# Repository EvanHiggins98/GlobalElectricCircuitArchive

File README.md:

# GlobalElectricCircuitArchive
This is an archive of the Global Electric Circuit Project's code repositories. This Repository was made to allow for all involved code to be found in one place at the conclusion of the project.

Original repositories Global Electric Circuit project repositories can be found at:

| Repository                                                                  | Description         |
|:--------------------------------------------------------------------------- |:------------------  |
| [GlobalCircuit](https://github.com/chordtoll/GlobalCircuit)                    | PIC32 code          |
| [GECaux](https://github.com/chordtoll/GECaux)                                  | PIC16 code          |
| [GECutils](https://github.com/chordtoll/GECutils)                              | Python scripts      |
| [LocalElectricCircuit](https://github.com/CodyAnderson/LocalElectricCircuit)| Circuit board files |

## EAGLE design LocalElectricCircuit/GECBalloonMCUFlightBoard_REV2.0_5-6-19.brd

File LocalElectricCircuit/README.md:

# LocalElectricCircuit

This is the repository containing the Circuit board files for the Global Electric Circuit project.

Other Global Electric Circuit project repositories can be found at:

| Repository                                                                  | Description         |
|:--------------------------------------------------------------------------- |:------------------  |
| [GlobalCircuit](https://github.com/chordtoll/GlobalCircuit)                    | PIC32 code          |
| [GECaux](https://github.com/chordtoll/GECaux)                                  | PIC16 code          |
| [GECutils](https://github.com/chordtoll/GECutils)                              | Python scripts      |
| [LocalElectricCircuit](https://github.com/CodyAnderson/LocalElectricCircuit)| Circuit board files |

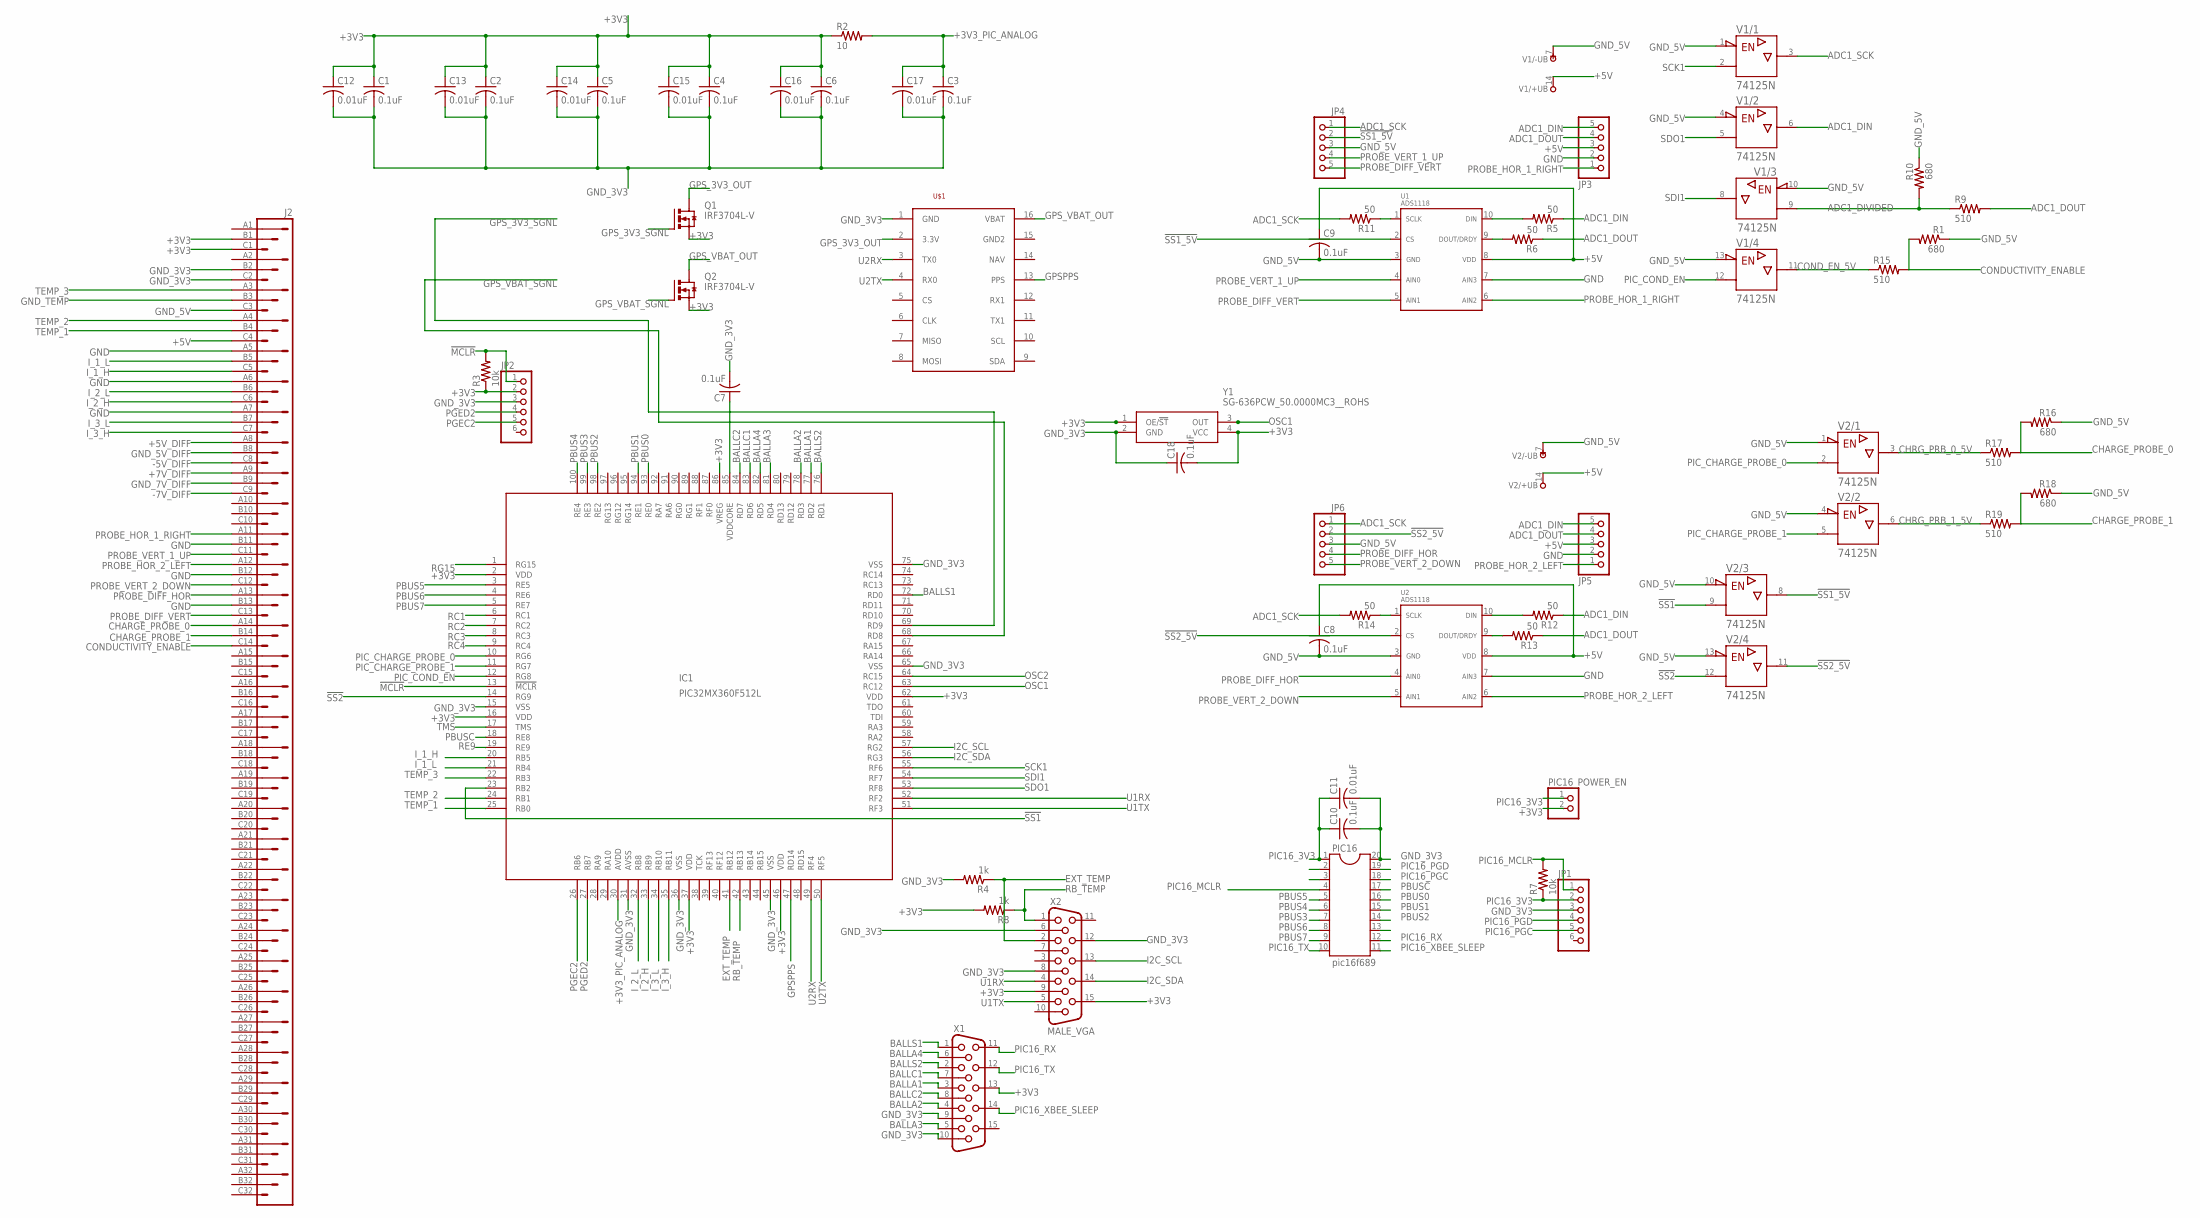
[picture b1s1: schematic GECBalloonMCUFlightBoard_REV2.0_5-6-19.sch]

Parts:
C1, C2, C3, C4, C5, C6, C7, C8, C9, C10, C18: 0.1uF; C1206
C11, C12, C13, C14, C15, C16, C17: 0.01uF; C1206
IC1: PIC32MX360F512L; TQFP100
J2: VG96KB
JP1, JP2: PINHD-1X6; 1X06
JP3, JP4, JP5, JP6: PINHD-1X5; 1X05
PIC16: pic16f689; DIL20
PIC16_POWER_EN: PINHD-1X2; 1X02
Q1, Q2: IRF3704L-V; TO262-V
R1, R10, R16, R18: 680; R1206
R2: 10; M1206
R3, R7: 10k; M1206
R4, R8: 1k; 0414/15
R5, R6, R11, R12, R13, R14: 50; M1206
R9, R15, R17, R19: 510; R1206
U1, U2: ADS1118; MSOP10
U$1: SPARKFUN_VENUS_GPS_BREAKOUT; SPARKFUN_BOARD
V1, V2: 74125N; DIL14
X1: HF15H; HDF15H
X2: MALE_VGA; MALE_PACKAGE
Y1: SG-636PCW_50.0000MC3__ROHS; SG-636

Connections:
!MCLR: IC1.13 (!MCLR), JP2.1, R3.2
!SS1: IC1.23 (RB2), V2.9 (A)
!SS1_5V: JP4.2, U1.2 (CS), V2.8 (Y)
!SS2: IC1.14 (RG9), V2.12 (A)
!SS2_5V: JP6.2, U2.2 (CS), V2.11 (Y)
+3V3: C1.1, C2.1, C4.1, C5.1, C6.1, C12.1, C13.1, C14.1, C15.1, C16.1, C18.2, IC1.2 (VDD), IC1.16 (VDD), IC1.37 (VDD), IC1.46 (VDD), IC1.62 (VDD), IC1.86 (VREG), J2.B1, J2.C1, JP2.2, PIC16_POWER_EN.2, Q1.3 (S), Q2.3 (S), R2.1, R3.1, R8.2, X1.13, X2.9, X2.15, Y1.1 (OE/!ST), Y1.4 (VCC)
+3V3_PIC_ANALOG: C3.1, C17.1, IC1.30 (AVDD), R2.2
+5V: C8.1, C9.1, J2.C4, JP3.3, JP5.3, U1.8 (VDD), U2.8 (VDD), V1.14 (+UB), V2.14 (+UB)
+5V_DIFF: J2.A8
+7V_DIFF: J2.A9
-5V_DIFF: J2.C8
-7V_DIFF: J2.C9
ADC1_DIN: JP3.5, JP5.5, R5.1, R12.1, V1.6 (Y)
ADC1_DIVIDED: R9.1, R10.2, V1.9 (A)
ADC1_DOUT: JP3.4, JP5.4, R6.1, R9.2, R13.1
ADC1_SCK: JP4.1, JP6.1, R11.2, R14.2, V1.3 (Y)
BALLA1: IC1.77 (RD2), X1.3
BALLA2: IC1.78 (RD3), X1.4
BALLA3: IC1.81 (RD4), X1.5
BALLA4: IC1.82 (RD5), X1.6
BALLC1: IC1.83 (RD6), X1.7
BALLC2: IC1.84 (RD7), X1.8
BALLS1: IC1.72 (RD0), X1.1
BALLS2: IC1.76 (RD1), X1.2
CHARGE_PROBE_0: J2.A14, R16.2, R17.2
CHARGE_PROBE_1: J2.B14, R18.2, R19.2
CHRG_PRB_0_5V: R17.1, V2.3 (Y)
CHRG_PRB_1_5V: R19.1, V2.6 (Y)
CONDUCTIVITY_ENABLE: J2.C14, R1.2, R15.2
COND_EN_5V: R15.1, V1.11 (Y)
EXT_TEMP: IC1.41 (RB12), R4.1, X2.2
GND: J2.A5, J2.A6, J2.A7, J2.B11, J2.B12, J2.B13, JP3.2, JP5.2, U1.7 (AIN3), U2.7 (AIN3)
GND_3V3: C1.2, C2.2, C3.2, C4.2, C5.2, C6.2, C7.2, C10.2, C11.2, C12.2, C13.2, C14.2, C15.2, C16.2, C17.2, C18.1, IC1.15 (VSS), IC1.31 (AVSS), IC1.36 (VSS), IC1.45 (VSS), IC1.65 (VSS), IC1.75 (VSS), J2.B2, J2.C2, JP1.3, JP2.3, PIC16.20, R4.2, U$1.1 (GND), X1.9, X1.10, X2.6, X2.8, X2.12, Y1.2 (GND)
GND_5V: C8.2, C9.2, J2.C3, JP4.3, JP6.3, R1.1, R10.1, R16.1, R18.1, U1.3 (GND), U2.3 (GND), V1.1 (!G), V1.4 (!G), V1.7 (-UB), V1.10 (!G), V1.13 (!G), V2.1 (!G), V2.4 (!G), V2.7 (-UB), V2.10 (!G), V2.13 (!G)
GND_5V_DIFF: J2.B8
GND_7V_DIFF: J2.B9
GND_TEMP: J2.B3
GPSPPS: IC1.47 (RD14), U$1.13 (PPS)
GPS_3V3_OUT: Q1.2 (D), U$1.2 (3.3V)
GPS_3V3_SGNL: IC1.69 (RD9), Q1.1 (G)
GPS_VBAT_OUT: Q2.2 (D), U$1.16 (VBAT)
GPS_VBAT_SGNL: IC1.68 (RD8), Q2.1 (G)
I2C_SCL: IC1.57 (RG2), X2.13
I2C_SDA: IC1.56 (RG3), X2.14
I_1_H: IC1.20 (RB5), J2.C5
I_1_L: IC1.21 (RB4), J2.B5
I_2_H: IC1.33 (RB9), J2.C6
I_2_L: IC1.32 (RB8), J2.B6
I_3_H: IC1.35 (RB11), J2.C7
I_3_L: IC1.34 (RB10), J2.B7
unnamed: R5.2, U1.10 (DIN)
unnamed: R6.2, U1.9 (DOUT/DRDY)
unnamed: R11.1, U1.1 (SCLK)
unnamed: R12.2, U2.10 (DIN)
unnamed: R13.2, U2.9 (DOUT/DRDY)
unnamed: R14.1, U2.1 (SCLK)
OSC1: IC1.63 (RC12), Y1.3 (OUT)
OSC2: IC1.64 (RC15)
PBUS0: IC1.93 (RE0), PIC16.16
PBUS1: IC1.94 (RE1), PIC16.15
PBUS2: IC1.98 (RE2), PIC16.14
PBUS3: IC1.99 (RE3), PIC16.7
PBUS4: IC1.100 (RE4), PIC16.6
PBUS5: IC1.3 (RE5), PIC16.5
PBUS6: IC1.4 (RE6), PIC16.8
PBUS7: IC1.5 (RE7), PIC16.9
PBUSC: IC1.18 (RE8), PIC16.17
PGEC2: IC1.26 (RB6), JP2.5
PGED2: IC1.27 (RB7), JP2.4
PIC16_3V3: C10.1, C11.1, JP1.2, PIC16.1, PIC16_POWER_EN.1, R7.1
PIC16_MCLR: JP1.1, PIC16.4, R7.2
PIC16_PGC: JP1.5, PIC16.18
PIC16_PGD: JP1.4, PIC16.19
PIC16_RX: PIC16.12, X1.11
PIC16_TX: PIC16.10, X1.12
PIC16_XBEE_SLEEP: PIC16.11, X1.14
PIC_CHARGE_PROBE_0: IC1.10 (RG6), V2.2 (A)
PIC_CHARGE_PROBE_1: IC1.11 (RG7), V2.5 (A)
PIC_COND_EN: IC1.12 (RG8), V1.12 (A)
PROBE_DIFF_HOR: J2.A13, JP6.4, U2.4 (AIN0)
PROBE_DIFF_VERT: J2.C13, JP4.5, U1.5 (AIN1)
PROBE_HOR_1_RIGHT: J2.A11, JP3.1, U1.6 (AIN2)
PROBE_HOR_2_LEFT: J2.A12, JP5.1, U2.6 (AIN2)
PROBE_VERT_1_UP: J2.C11, JP4.4, U1.4 (AIN0)
PROBE_VERT_2_DOWN: J2.C12, JP6.5, U2.5 (AIN1)
RB_TEMP: IC1.42 (RB13), R8.1, X2.1
RC1: IC1.6 (RC1)
RC2: IC1.7 (RC2)
RC3: IC1.8 (RC3)
RC4: IC1.9 (RC4)
RE9: IC1.19 (RE9)
RG15: IC1.1 (RG15)
SCK1: IC1.55 (RF6), V1.2 (A)
SDI1: IC1.54 (RF7), V1.8 (Y)
SDO1: IC1.53 (RF8), V1.5 (A)
TEMP_1: IC1.25 (RB0), J2.B4
TEMP_2: IC1.24 (RB1), J2.A4
TEMP_3: IC1.22 (RB3), J2.A3
TMS: IC1.17 (TMS)
U1RX: IC1.52 (RF2), X2.4
U1TX: IC1.51 (RF3), X2.5
U2RX: IC1.49 (RF4), U$1.3 (TX0)
U2TX: IC1.50 (RF5), U$1.4 (RX0)
VCAP/VCORE: C7.1, IC1.85 (VDDCORE)

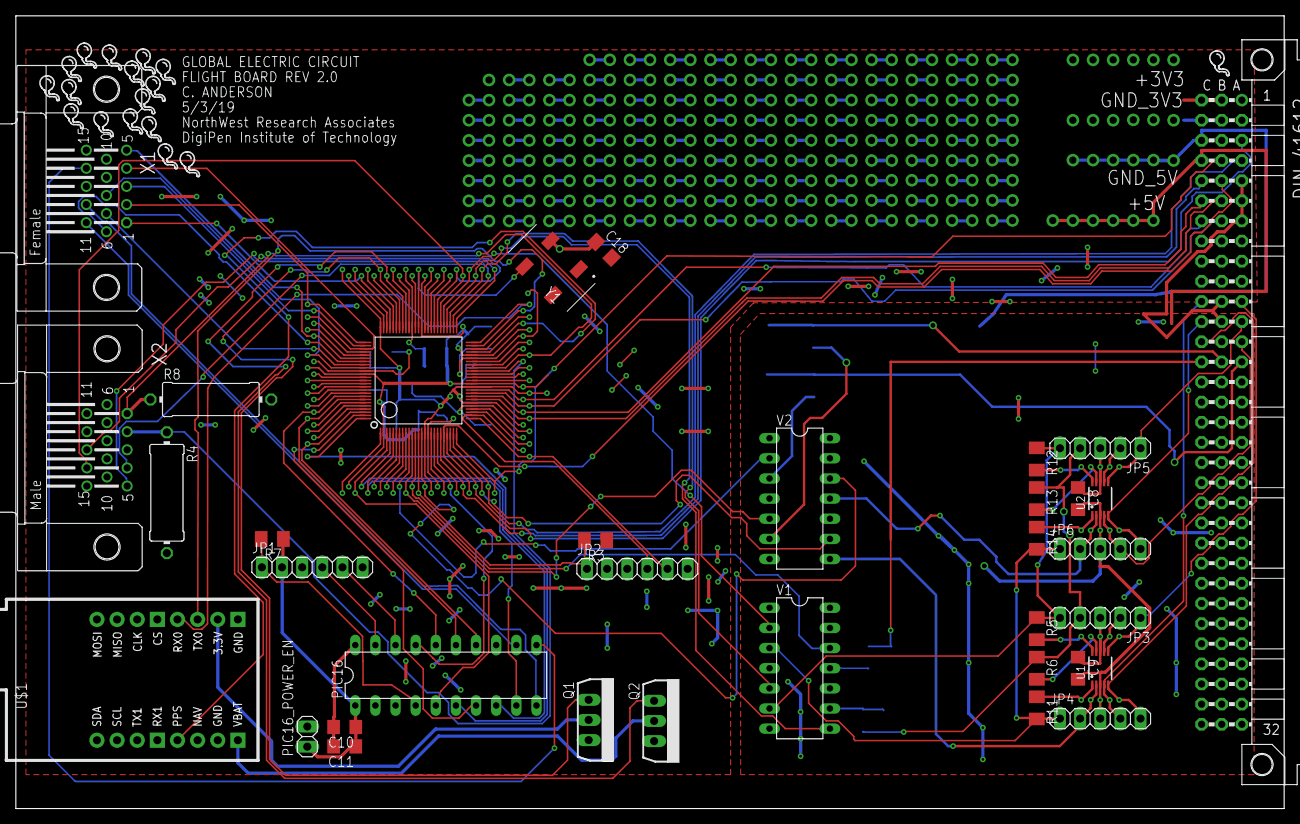
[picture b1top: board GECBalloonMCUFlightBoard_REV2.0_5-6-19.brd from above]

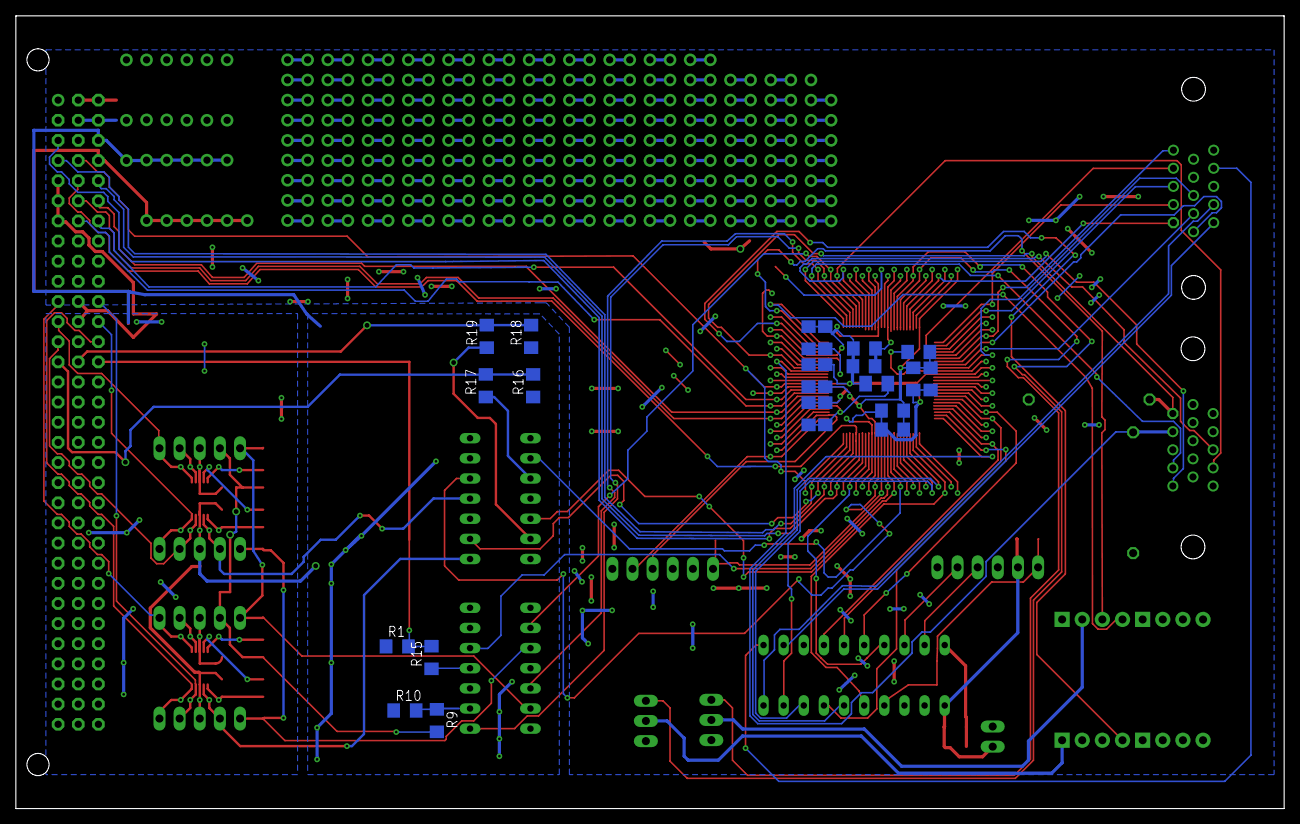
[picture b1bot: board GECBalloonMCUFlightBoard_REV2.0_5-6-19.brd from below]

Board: 2 copper layers, 160.0 x 100.0 mm, 74 parts (22 on the bottom side), 89 nets.

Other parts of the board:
U$2, U$3, U$4, U$5, U$6, U$7, U$8, U$9, U$10, U$11, U$12, U$14, U$15, U$16, U$17, U$19, U$21: BALLOON

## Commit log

2021-07-24 Fixed README.md
2021-07-24 Removed last line of README.md
2021-07-24 First Code Commit
2021-07-24 added missing repo code
2021-07-24 Added missing files
2021-07-24 removed nested gits
2021-07-24 removed sensative data
2021-07-24 refixed README.md
2021-07-24 fixed groundstation version
2021-07-25 re-removed nested git after fixing ground station version
2021-07-25 Added missing comments on functions
2021-07-25 Updated ground station documentation
2021-07-25 Added ground station documentation regarding the GPS map
2021-07-25 merged GroundStation Branch
